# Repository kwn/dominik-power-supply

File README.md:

# dominik-power-supply
KiCad project for Dominik power supply

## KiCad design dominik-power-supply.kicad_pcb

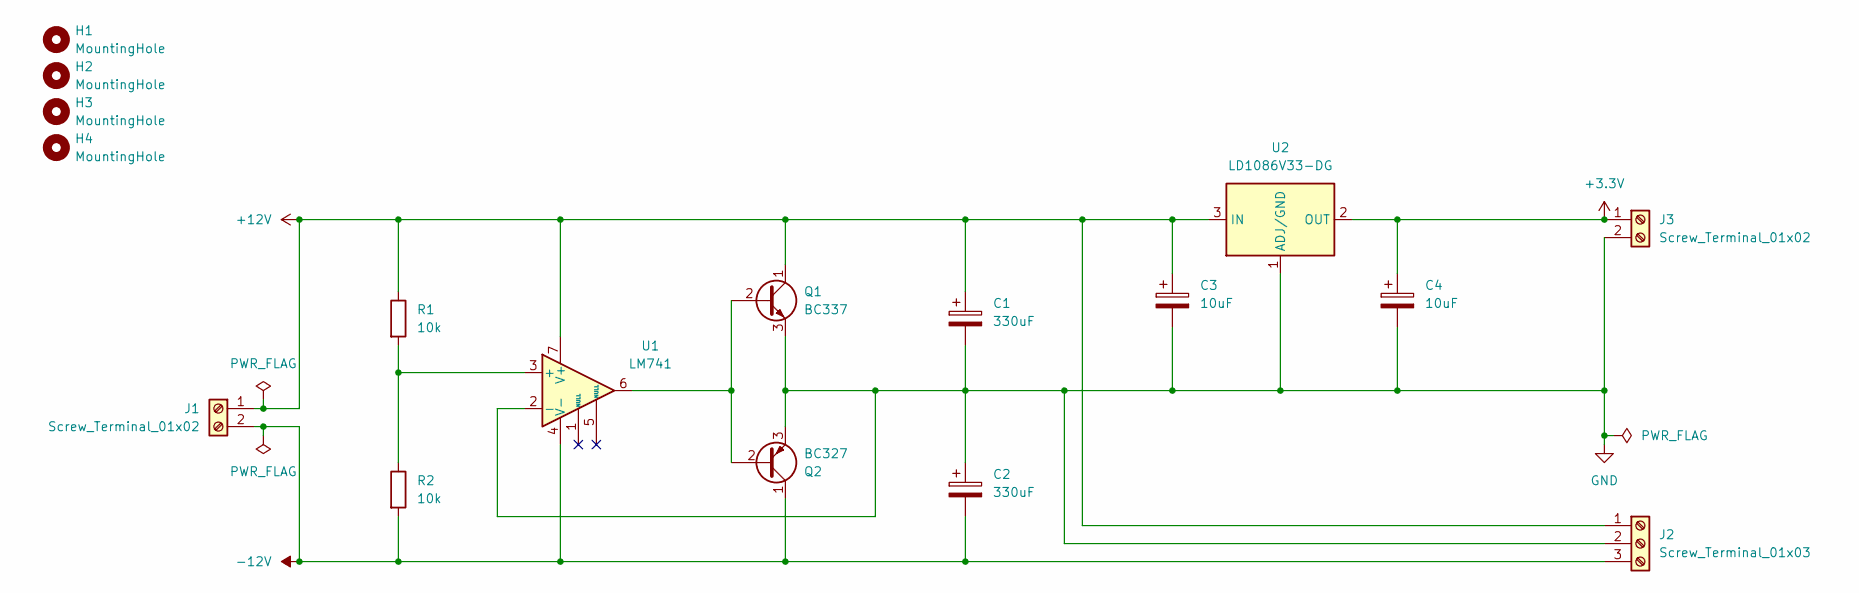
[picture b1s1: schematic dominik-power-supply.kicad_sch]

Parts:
C1, C2: 330uF; CP_Radial_D8.0mm_P3.50mm
C3, C4: 10uF; CP_Radial_D5.0mm_P2.00mm
H1, H2, H3, H4: MountingHole; MountingHole_3.2mm_M3
J1, J3: Screw_Terminal_01x02; TerminalBlock_Phoenix_PT-1,5-2-5.0-H_1x02_P5.00mm_Horizontal
J2: Screw_Terminal_01x03; TerminalBlock_Phoenix_PT-1,5-3-5.0-H_1x03_P5.00mm_Horizontal
Q1: BC337; TO-92_Inline
Q2: BC327; TO-92_Inline
R1, R2: 10k; R_Axial_DIN0207_L6.3mm_D2.5mm_P10.16mm_Horizontal
U1: LM741; DIP-8_W7.62mm_Socket
U2: LD1086V33-DG; TO-220-3_Vertical

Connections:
+3.3V: C4.1, J3.1, U2.2 (OUT)
+12V: C1.1, C3.1, J1.1, J2.1, Q1.1 (C), R1.1, U1.7 (V+), U2.3 (IN)
-12V: C2.2, J1.2, J2.3, Q2.1 (C), R2.2, U1.4 (V-)
GND: C1.2, C2.1, C3.2, C4.2, J2.2, J3.2, Q1.3 (E), Q2.3 (E), U1.2 (-), U2.1 (ADJ/GND)
unnamed: Q1.2 (B), Q2.2 (B), U1.6
unnamed: R1.2, R2.1, U1.3 (+)

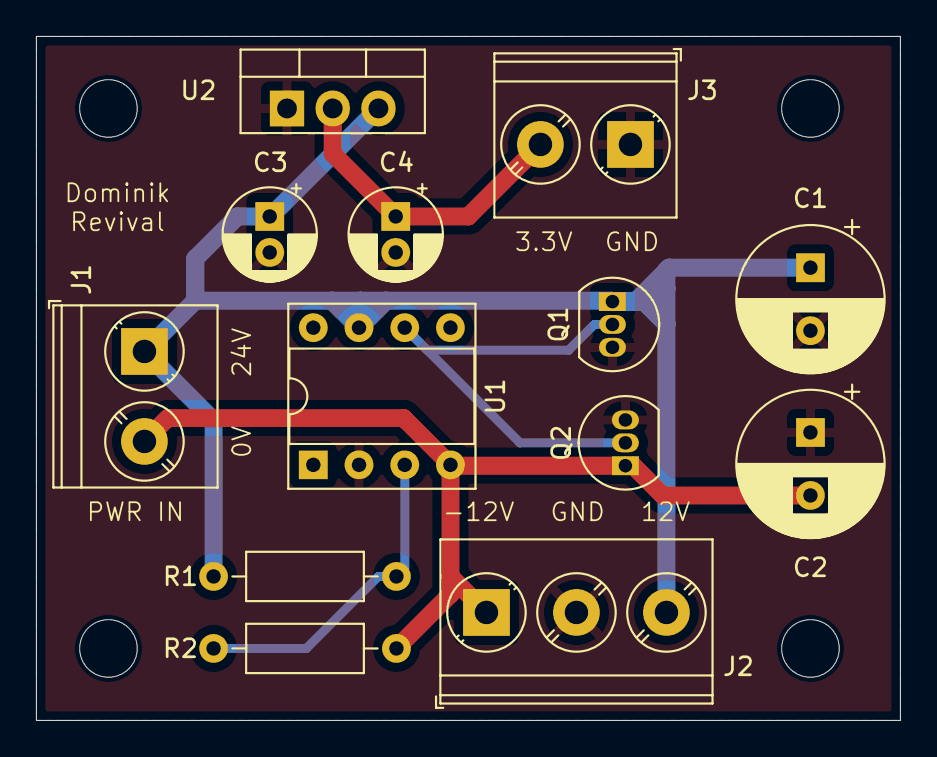
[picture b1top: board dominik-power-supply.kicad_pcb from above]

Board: 2 copper layers, 48.0 x 38.0 mm, 17 parts (0 on the bottom side), 6 nets.
